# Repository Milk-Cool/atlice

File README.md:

# atlice
attiny85-based multi-purpose lice hairclips

<small>[head image source](https://en.wiktionary.org/wiki/head)</small>

## what is this?
this is a hairclip that can be used as either a mood indicator, a tamagotchi, or a portable weather station. well, not a hairclip by itself -- a pcb that can be attached onto a hairclip with rubber bands. it has multiple firmware modes available, all of which let you use the device in their own unique ways. it is based on the attiny85 chip, which isn't too powerful but is more than enough for this.

## how do i use this?
first of all, get all the required components (listed in `bom.xml`, disregard components you don't need) and build it! the gerber files and the source project files are in this repo, too (see `kicad/`). here are some notes:
- get an SSD1306 display that a. works via i2c and b. has the power pin on the left. from what i could find, these also take 3V as the input just fine, which is perfect for our purposes since we use a CR2302 battery. (note: some sellers might send you the wrong type of display, like mine! please be aware of that)
- solder a 150Ohm resistor at J5-J6 and a 100Ohm resistor at J7-J8 and J9-J10.
- solder/attach the SSD1306 display facing inwards at J2, and the BMP180 temperature sensor also facing inwards at J3. the attiny85 goes at U1.
- attach the battery case at J1, with the top pin being the ground pin and the bottom pin being the +3V0 pin.

you can then attach it to a hairclip using small rubber bands with the grooves on the pcb (the "legs" of the louse).

once you have built it, flash the attiny85 with the appropriate firmware from `firmware/`. (note: if you want to permanently solder the attiny85 to the board, flash it before that! it'll be very hard to do it otherwise.)
then just turn on the battery and enjoy!!

### controls
|mode|FUN|RST|
|-|-|-|
|mood indicator|-|change color/mood|
|weather station|-|turn on|
|tamagotchi|play with|feed/turn on|

## why was this made?
i have an old mood indicator hairclip (inspired by a pi pico hot glued to a hairclip, which was gifted to me by a friend), which also has an attiny85. i built it around december of 2025, and wanted to push the concept of wearable hairclips even further ever since then. this is my next attempt, hopefully it's actually good!!

## credits
- zine background: https://www.dreamstime.com/illustration/bug-wallpaper.html

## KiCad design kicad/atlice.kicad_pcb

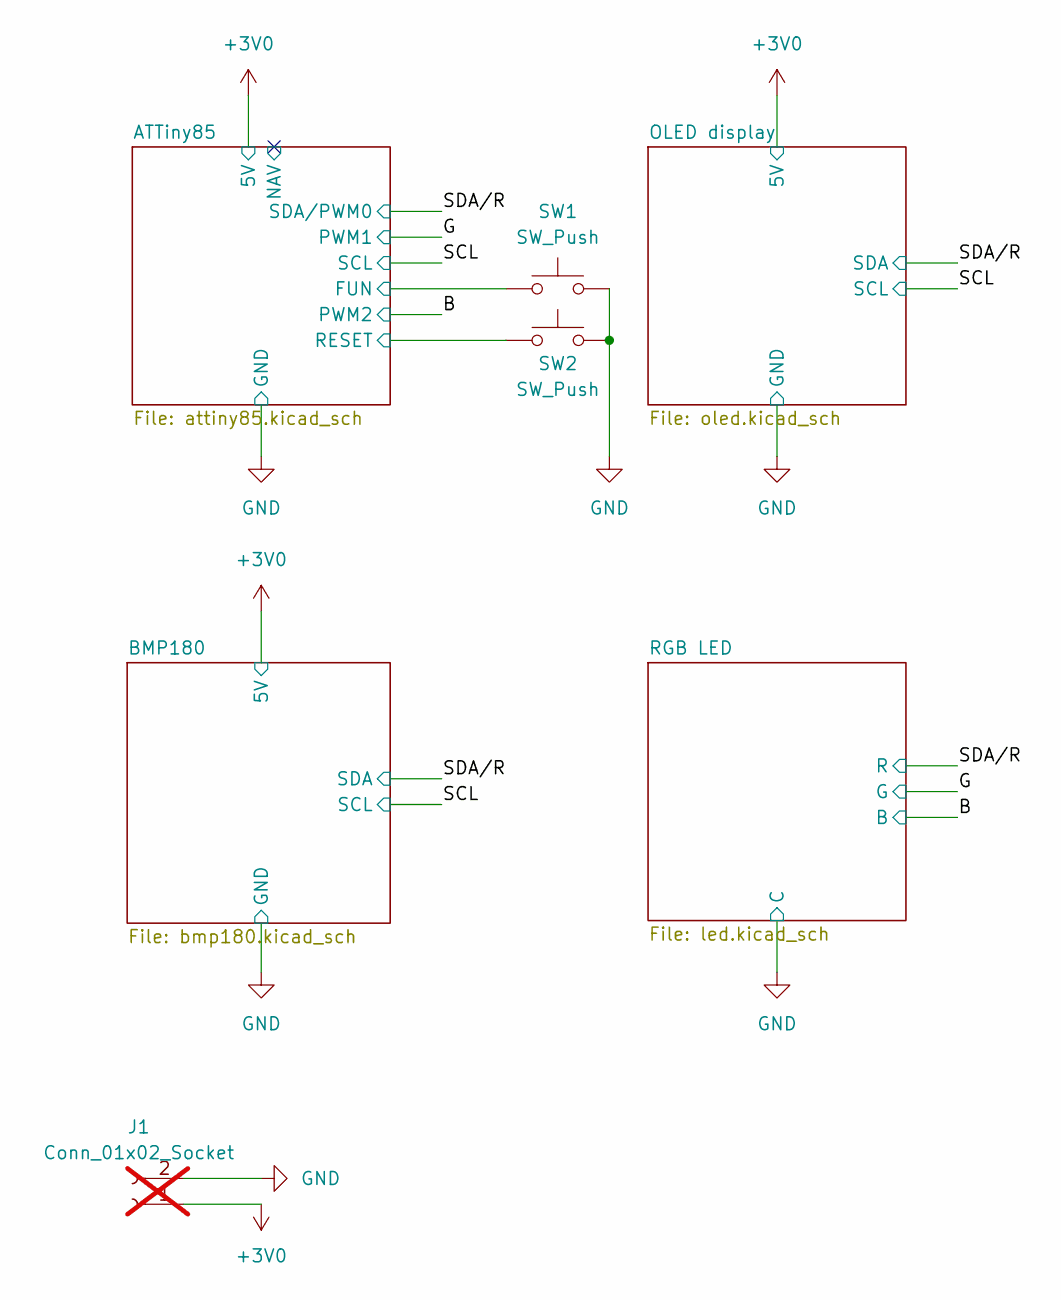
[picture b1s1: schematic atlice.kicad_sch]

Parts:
J1: Conn_01x02_Socket; PinHeader_1x02_P2.54mm_Vertical; not fitted
SW1, SW2: SW_Push; SW_PUSH_6mm

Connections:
+3V0: J1.1; also elsewhere on the board
/ATTiny85/FUN: SW1.1; also elsewhere on the board
/ATTiny85/RESET: SW2.1; also elsewhere on the board
GND: J1.2, SW1.2, SW2.2; also elsewhere on the board

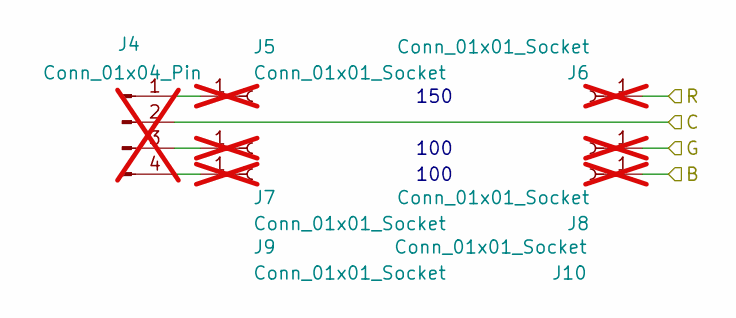
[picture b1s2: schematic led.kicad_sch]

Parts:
J4: Conn_01x04_Pin; PinSocket_1x04_P2.54mm_Vertical; not fitted
J5, J6, J7, J8, J9, J10: Conn_01x01_Socket; PinSocket_1x01_P2.54mm_Vertical; not fitted

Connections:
/B: J10.1 (Pin_1_1); also elsewhere on the board
/G: J8.1 (Pin_1_1); also elsewhere on the board
/SDA/R: J6.1 (Pin_1_1); also elsewhere on the board
GND: J4.2; also elsewhere on the board
unnamed: J4.1, J5.1 (Pin_1_1)
unnamed: J4.3, J7.1 (Pin_1_1)
unnamed: J4.4, J9.1 (Pin_1_1)

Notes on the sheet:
100
150

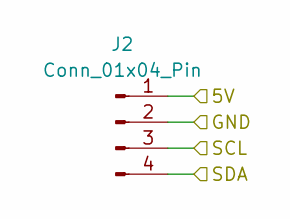
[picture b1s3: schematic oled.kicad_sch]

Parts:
J2: Conn_01x04_Pin; PinSocket_1x04_P2.54mm_Vertical

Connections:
+3V0: J2.1; also elsewhere on the board
/SCL: J2.3; also elsewhere on the board
/SDA/R: J2.4; also elsewhere on the board
GND: J2.2; also elsewhere on the board

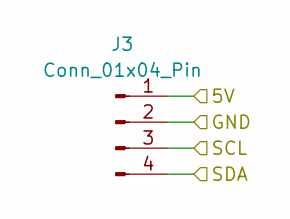
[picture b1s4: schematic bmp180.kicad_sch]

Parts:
J3: Conn_01x04_Pin; PinSocket_1x04_P2.54mm_Vertical

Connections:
+3V0: J3.1; also elsewhere on the board
/SCL: J3.3; also elsewhere on the board
/SDA/R: J3.4; also elsewhere on the board
GND: J3.2; also elsewhere on the board

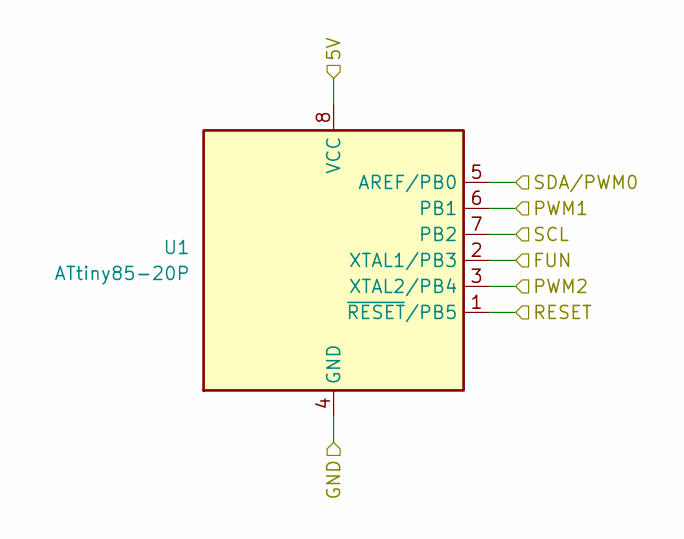
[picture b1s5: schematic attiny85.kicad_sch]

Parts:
U1: ATtiny85-20P; DIP-8_W7.62mm

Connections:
+3V0: U1.8 (VCC); also elsewhere on the board
/ATTiny85/FUN: U1.2 (XTAL1/PB3); also elsewhere on the board
/ATTiny85/RESET: U1.1 (~RESET/PB5); also elsewhere on the board
/B: U1.3 (XTAL2/PB4); also elsewhere on the board
/G: U1.6 (PB1); also elsewhere on the board
/SCL: U1.7 (PB2); also elsewhere on the board
/SDA/R: U1.5 (AREF/PB0); also elsewhere on the board
GND: U1.4 (GND); also elsewhere on the board

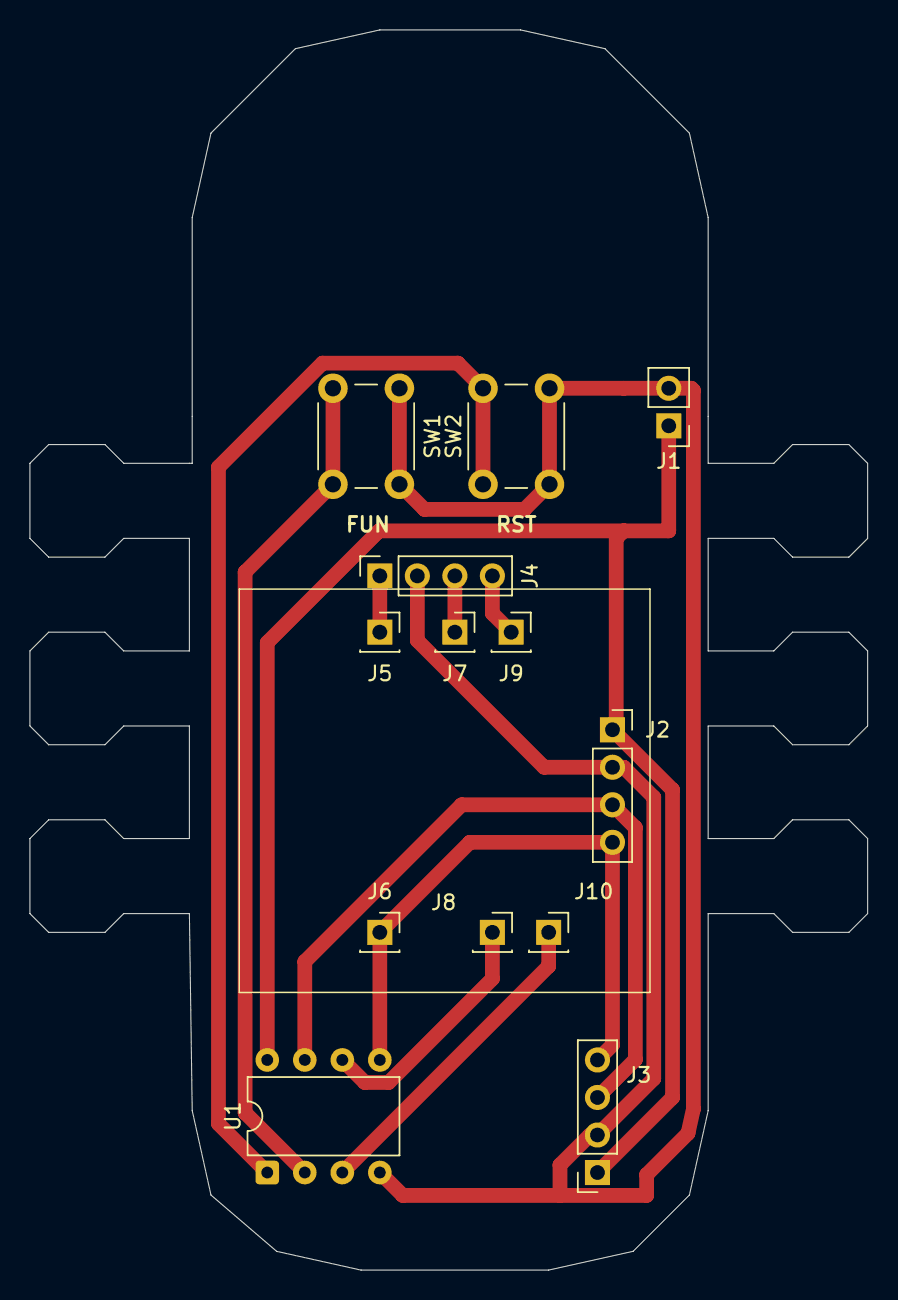
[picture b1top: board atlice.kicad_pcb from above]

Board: 2 copper layers, 56.7 x 83.9 mm, 13 parts (0 on the bottom side), 11 nets.

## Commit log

2026-06-12 code for all three modes
2026-06-12 tidy up the repo, add bom and csv and everything besides the zine
2026-06-12 add zine
2026-06-12 oops
2026-06-18 some fixes
2026-06-20 update zine
2026-06-20 add a photo
